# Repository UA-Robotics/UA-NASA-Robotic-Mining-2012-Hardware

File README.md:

# UA-NASA-Robotic-Mining-2012-Hardware

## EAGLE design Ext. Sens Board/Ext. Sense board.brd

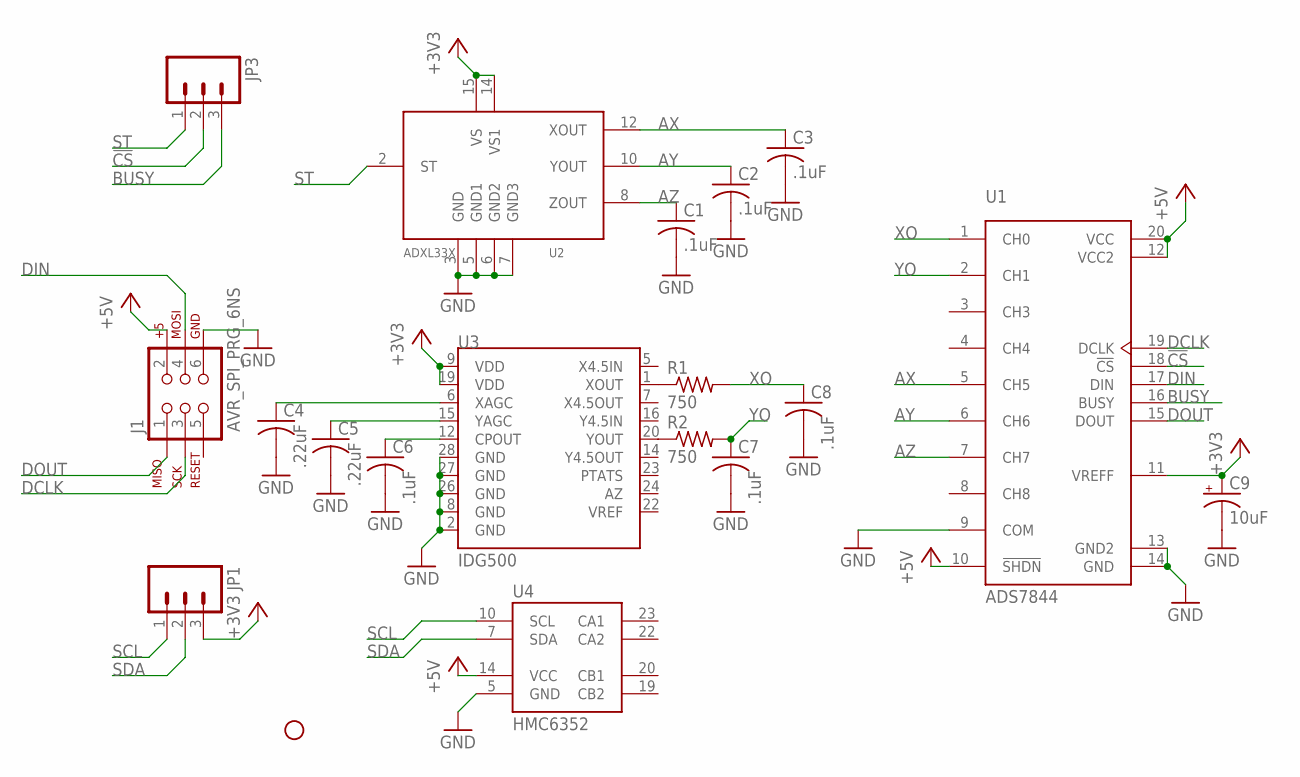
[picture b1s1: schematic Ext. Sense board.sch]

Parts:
C1, C2, C3, C6, C7, C8: .1uF; C0805
C4, C5: .22uF; C0805
C9: 10uF; POLC1206
J1: AVR_SPI_PRG_6NS; 2X3-NS
JP1, JP3: M031X03_NO_SILK; 1X03_NO_SILK
JP2: STAND-OFF
R1, R2: 750; R0805
U1: ADS7844; SSOP-20
U2: ADXL33X; 16LCSP
U3: IDG500; SPARKFUN_IDG500
U4: HMC6352; LCC24

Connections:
!CS: JP3.2, U1.18 (!CS)
+3V3: C9.1 (+), JP1.3, U1.11 (VREFF), U2.14 (VS1), U2.15 (VS), U3.9 (VDD), U3.19 (VDD)
+5V: J1.2, U1.10 (!SHDN), U1.12 (VCC2), U1.20 (VCC), U4.14 (VCC)
AX: C3.1, U1.5 (CH5), U2.12 (XOUT)
AY: C2.1, U1.6 (CH6), U2.10 (YOUT)
AZ: C1.1, U1.7 (CH7), U2.8 (ZOUT)
BUSY: JP3.3, U1.16 (BUSY)
DCLK: J1.3, U1.19 (DCLK)
DIN: J1.4, U1.17 (DIN)
DOUT: J1.1, U1.15 (DOUT)
GND: C1.2, C2.2, C3.2, C4.2, C5.2, C6.2, C7.2, C8.2, C9.2 (-), J1.6, U1.9 (COM), U1.13 (GND2), U1.14 (GND), U2.3 (GND), U2.5 (GND1), U2.6 (GND2), U2.7 (GND3), U3.2 (GND), U3.8 (GND), U3.26 (GND), U3.27 (GND), U3.28 (GND), U4.5 (GND)
unnamed: C4.1, U3.6 (XAGC)
unnamed: C5.1, U3.15 (YAGC)
unnamed: C6.1, U3.12 (CPOUT)
unnamed: R1.1, U3.1 (XOUT)
unnamed: R2.1, U3.20 (YOUT)
SCL: JP1.1, U4.10 (SCL)
SDA: JP1.2, U4.7 (SDA)
ST: JP3.1, U2.2 (ST)
XO: C8.1, R1.2, U1.1 (CH0)
YO: C7.1, R2.2, U1.2 (CH1)

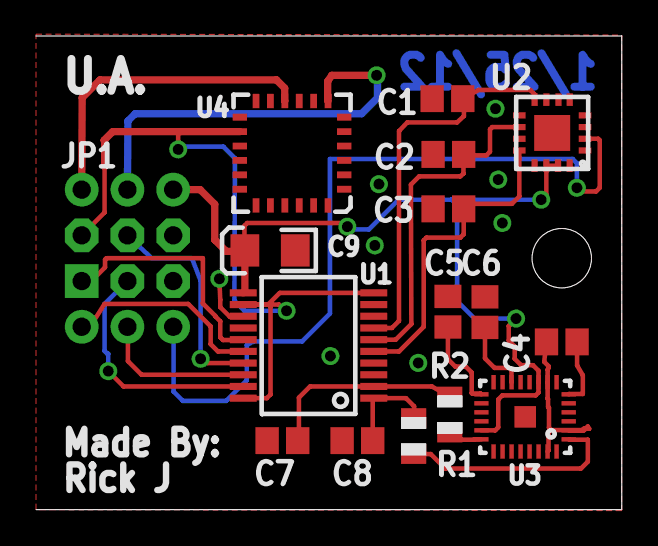
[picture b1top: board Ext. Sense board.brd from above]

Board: 2 copper layers, 32.5 x 26.3 mm, 19 parts (0 on the bottom side), 21 nets.

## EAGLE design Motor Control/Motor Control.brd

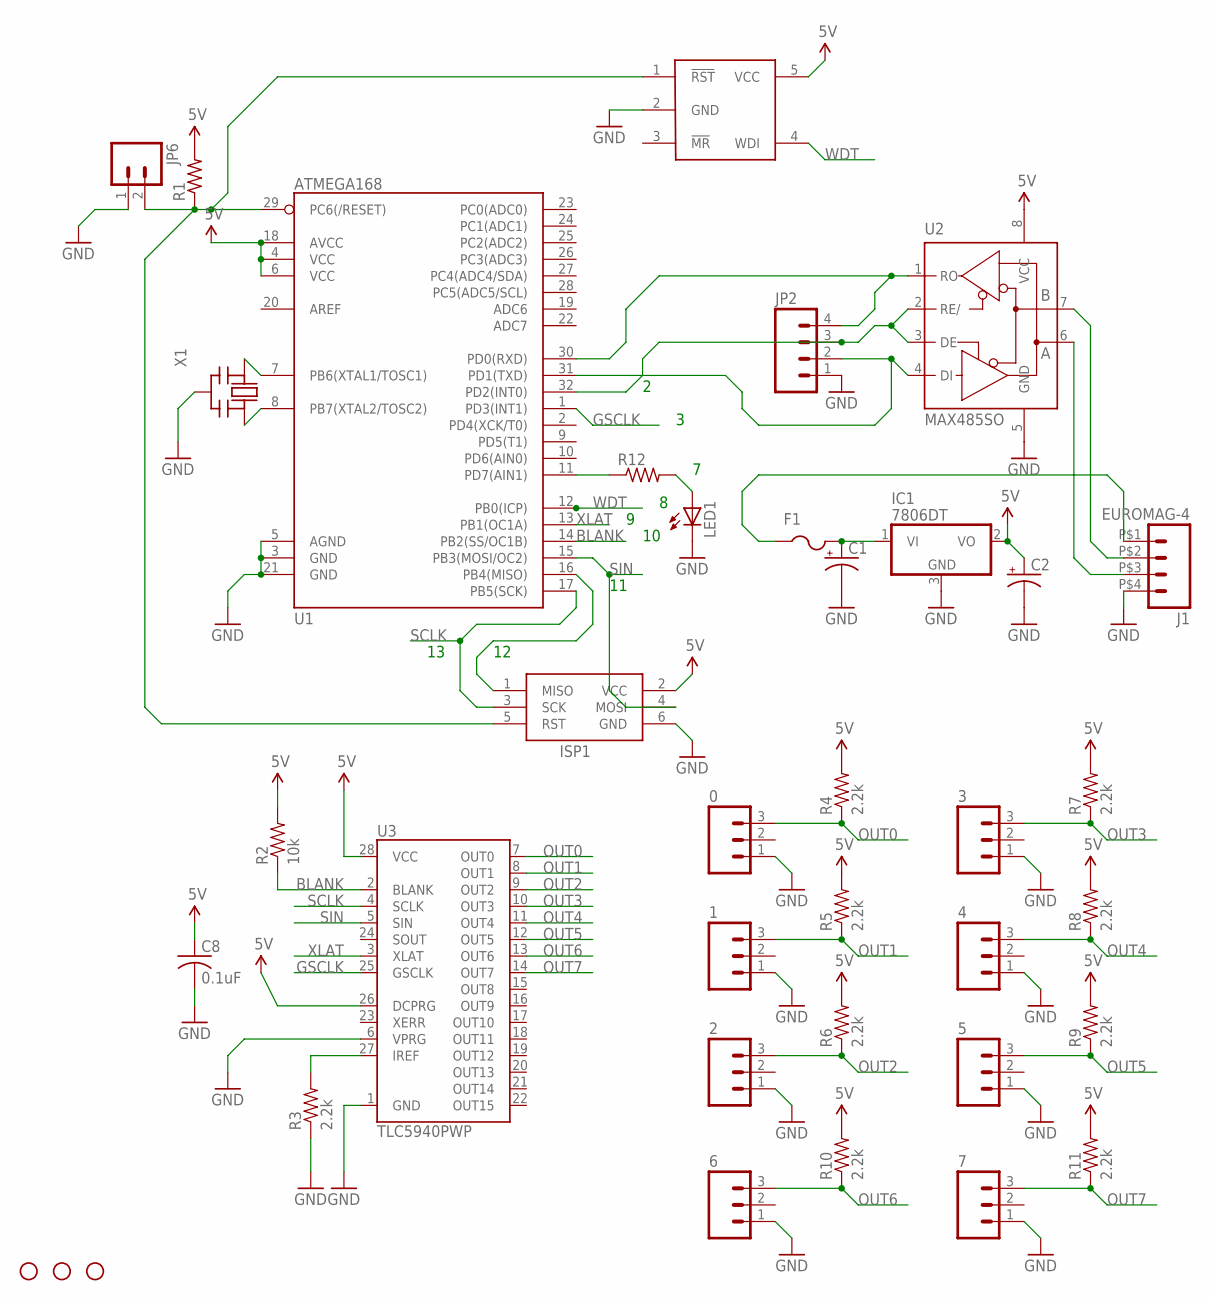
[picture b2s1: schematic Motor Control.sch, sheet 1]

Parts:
0, 1, 2, 3, 4, 5, 6, 7: M03PTH; 1X03
C1: CPOL-USCT7343; CT7343
C2: CPOL-USCT6032; CT6032
C8: 0.1uF; C0603
F1: PTCFUSE-1812; 1812
IC1: 7806DT; TO252
ISP1: AVRISP-6; AVRISP
J1: EUROMAG-4; M4
JP2: M04PTH; 1X04
JP3, JP4, JP5: STAND-OFF
JP6: M02LOCK_LONGPADS; 1X02_LOCK_LONGPADS
LED1: LEDCHIPLED_0805; CHIPLED_0805
R1, R12: R-US_M0805; M0805
R2: 10k; 0805
R3, R4, R5, R6, R7, R8, R9, R10, R11: 2.2k; 0805
U1: ATMEGA168; TQFP32-08
U2: MAX485SO; SO08
U3: TLC5940PWP; TSSOP28-GROUNDPAD
U$18: MAX823; SOT23-5L
X1: CERMOSCILL-AWCSR; AWCSR

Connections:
5V: C2.+, C8.1, IC1.2 (VO), ISP1.2 (VCC), R1.2, R2.2, R4.2, R5.2, R6.2, R7.2, R8.2, R9.2, R10.2, R11.2, U1.4 (VCC), U1.6 (VCC), U1.18 (AVCC), U2.8 (VCC), U3.26 (DCPRG), U3.28 (VCC), U$18.5 (VCC)
BLANK: R2.1, U1.14 (PB2(SS/OC1B)), U3.2 (BLANK)
GND: 0.1, 1.1, 2.1, 3.1, 4.1, 5.1, 6.1, 7.1, C1.-, C2.-, C8.2, IC1.3 (GND), ISP1.6 (GND), J1.P$4 (4), JP2.1, JP6.1, LED1.C, R3.1, U1.3 (GND), U1.5 (AGND), U1.21 (GND), U2.5 (GND), U3.1 (GND), U3.6 (VPRG), U$18.2 (GND), X1.2 (GND); also elsewhere on the board
GSCLK: U1.1 (PD3(INT1)), U3.25 (GSCLK)
unnamed: JP2.3, U1.32 (PD2(INT0)), U2.2 (RE/), U2.3 (DE)
unnamed: JP2.4, U1.30 (PD0(RXD)), U2.1 (RO)
unnamed: JP2.2, U1.31 (PD1(TXD)), U2.4 (DI)
unnamed: ISP1.5 (RST), JP6.2, R1.1, U1.29 (PC6(/RESET)), U$18.1 (!RST)
unnamed: U1.8 (PB7(XTAL2/TOSC2)), X1.3 (OUT)
unnamed: F1.1, J1.P$1 (1)
unnamed: ISP1.1 (MISO), U1.16 (PB4(MISO))
unnamed: C1.+, F1.2, IC1.1 (VI)
unnamed: U1.7 (PB6(XTAL1/TOSC1)), X1.1 (IN)
unnamed: R3.2, U3.27 (IREF)
unnamed: J1.P$2 (2), U2.7 (B)
unnamed: J1.P$3 (3), U2.6 (A)
unnamed: R12.1, U1.11 (PD7(AIN1))
unnamed: LED1.A, R12.2
OUT0: 0.3, R4.1, U3.7 (OUT0)
OUT1: 1.3, R5.1, U3.8 (OUT1)
OUT2: 2.3, R6.1, U3.9 (OUT2)
OUT3: 3.3, R7.1, U3.10 (OUT3)
OUT4: 4.3, R8.1, U3.11 (OUT4)
OUT5: 5.3, R9.1, U3.12 (OUT5)
OUT6: 6.3, R10.1, U3.13 (OUT6)
OUT7: 7.3, R11.1, U3.14 (OUT7)
SCLK: ISP1.3 (SCK), U1.17 (PB5(SCK)), U3.4 (SCLK)
SIN: ISP1.4 (MOSI), U1.15 (PB3(MOSI/OC2)), U3.5 (SIN)
WDT: U1.12 (PB0(ICP)), U$18.4 (WDI)
XLAT: U1.13 (PB1(OC1A)), U3.3 (XLAT)

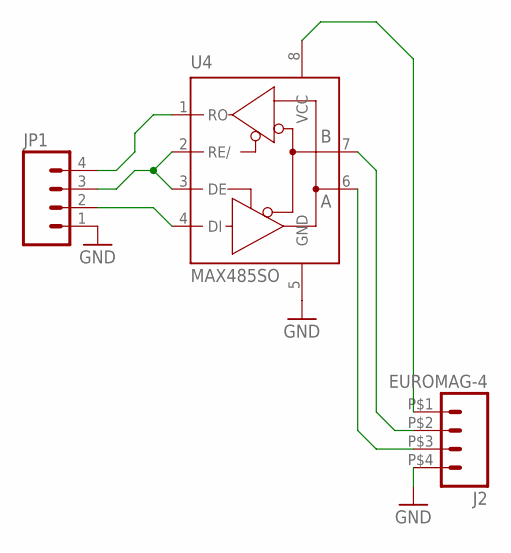
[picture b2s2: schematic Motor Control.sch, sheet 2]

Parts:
J2: EUROMAG-4; M4
JP1: M04PTH; 1X04
U4: MAX485SO; SO08

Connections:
GND: J2.P$4 (4), JP1.1, U4.5 (GND); also elsewhere on the board
unnamed: JP1.3, U4.2 (RE/), U4.3 (DE)
unnamed: JP1.4, U4.1 (RO)
unnamed: JP1.2, U4.4 (DI)
unnamed: J2.P$1 (1), U4.8 (VCC)
unnamed: J2.P$2 (2), U4.7 (B)
unnamed: J2.P$3 (3), U4.6 (A)

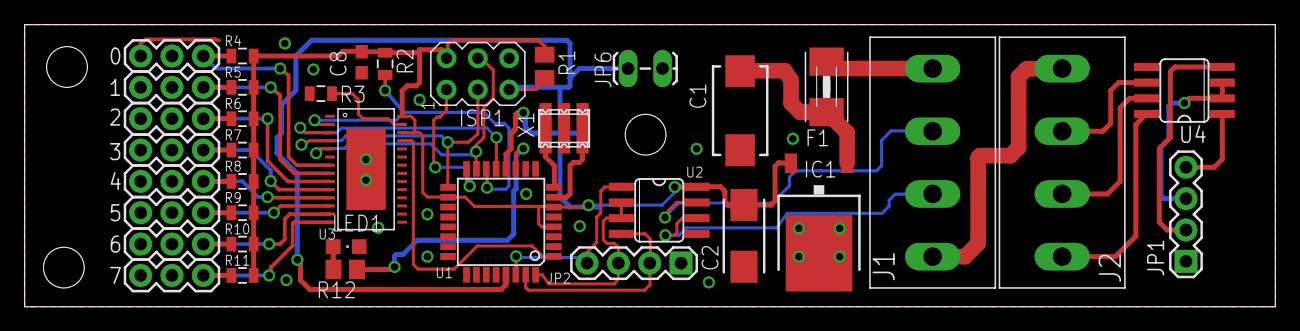
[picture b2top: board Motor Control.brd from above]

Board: 2 copper layers, 101.3 x 22.9 mm, 41 parts (1 on the bottom side), 36 nets.

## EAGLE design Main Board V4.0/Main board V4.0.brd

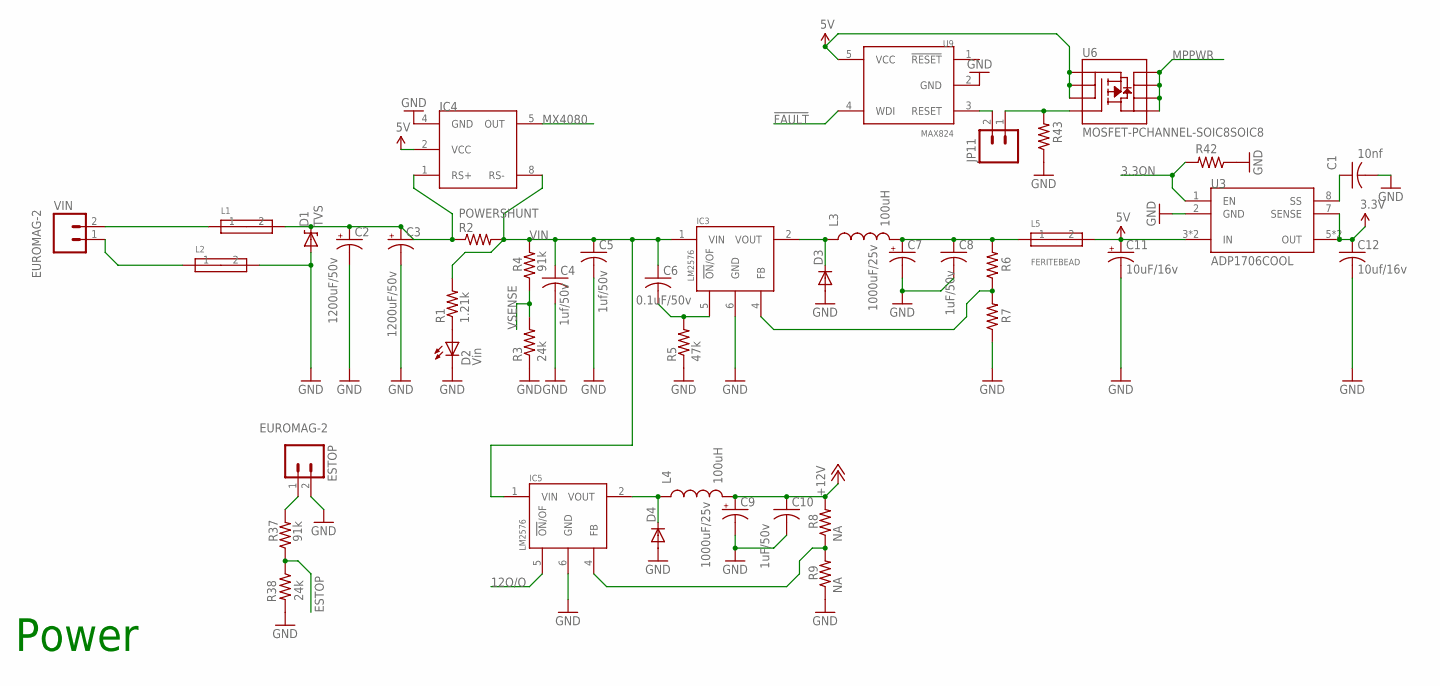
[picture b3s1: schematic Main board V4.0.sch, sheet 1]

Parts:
C1: 10nf; C0805
C2, C3: 1200uF/50v; CAN_18MM
C4, C5: 1uf/50v; C0805
C6: 0.1uF/50v; C0805
C7, C9: 1000uF/25v; CAN_18MM
C8, C10: 1uF/50v; C0805
C11: 10uF/16v; E3,5-10
C12: 10uf/16v; C0805
D1: TVS; DO-214AC
D2: Vin; CHIP-LED0805
D3, D4: DIODE-SMC; SMC
ESTOP: EUROMAG-2; M2
IC3, IC5: LM2576; TO-263-5
IC4: MAX4080; SO08
JP11: M02LOCK_LONGPADS; 1X02_LOCK_LONGPADS
L1, L2, L5: FERITEBEAD; 0603
L3, L4: 100uH; INDUCTOR_5X3
R1: 1.21k; R0805
R2: POWERSHUNT; RW3R5EAR100JE
R3, R38: 24k; R0805
R4, R37: 91k; R0805
R5: 47k; R0805
R6, R7, R8, R9, R42, R43: NA; R0805
U3: ADP1706COOL; SO-8COOL
U6: MOSFET-PCHANNEL-SOIC8SOIC8; SO08
U9: MAX824; SOT-5L
VIN: EUROMAG-2; M2

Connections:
3.3ON: R42.2, U3.1 (EN); also elsewhere on the board
3.3V: C12.1, U3.5 (OUT), U3.6 (OUT), U3.7 (SENSE); also elsewhere on the board
5V: C11.+, IC4.2 (VCC), L5.2, U3.3 (IN), U3.4 (IN), U6.1 (S), U6.2 (S), U6.3 (S), U9.5 (VCC); also elsewhere on the board
12O/O: IC5.5 (!ON!/OF); also elsewhere on the board
!FAULT: U9.4 (WDI); also elsewhere on the board
+12V: C9.+, C10.1, L4.2, R8.2; also elsewhere on the board
ESTOP: R37.1, R38.1; also elsewhere on the board
GND: C1.2, C2.-, C3.-, C4.2, C5.2, C7.-, C8.2, C9.-, C10.2, C11.-, C12.2, D1.A, D2.C, D3.A, D4.A, ESTOP.2, IC3.6 (GND), IC4.4 (GND), IC5.6 (GND), L2.2, R3.1, R5.1, R7.1, R9.1, R38.2, R42.1, R43.1, U3.2 (GND), U9.2 (GND); also elsewhere on the board
MPPWR: U6.5 (D), U6.6 (D), U6.7 (D), U6.8 (D); also elsewhere on the board
MX4080: IC4.5 (OUT); also elsewhere on the board
unnamed: C6.2, IC3.5 (!ON!/OF), R5.2
unnamed: D4.C, IC5.2 (VOUT), L4.1
unnamed: D3.C, IC3.2 (VOUT), L3.1
unnamed: JP11.1, R43.2, U6.4 (G)
unnamed: JP11.2, U9.3 (RESET)
unnamed: L1.1, VIN.2
unnamed: ESTOP.1, R37.2
unnamed: C2.+, C3.+, D1.C, IC4.1 (RS+), L1.2, R2.1
unnamed: IC3.4 (FB), R6.1, R7.2
unnamed: IC5.4 (FB), R8.1, R9.2
unnamed: D2.A, R1.1
unnamed: L2.1, VIN.1
unnamed: C7.+, C8.1, L3.2, L5.1, R6.2
unnamed: C1.1, U3.8 (SS)
VIN: C4.1, C5.1, C6.1, IC3.1 (VIN), IC4.8 (RS-), IC5.1 (VIN), R1.2, R2.2, R4.2
VSENSE: R3.2, R4.1; also elsewhere on the board

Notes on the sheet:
Power
IC4

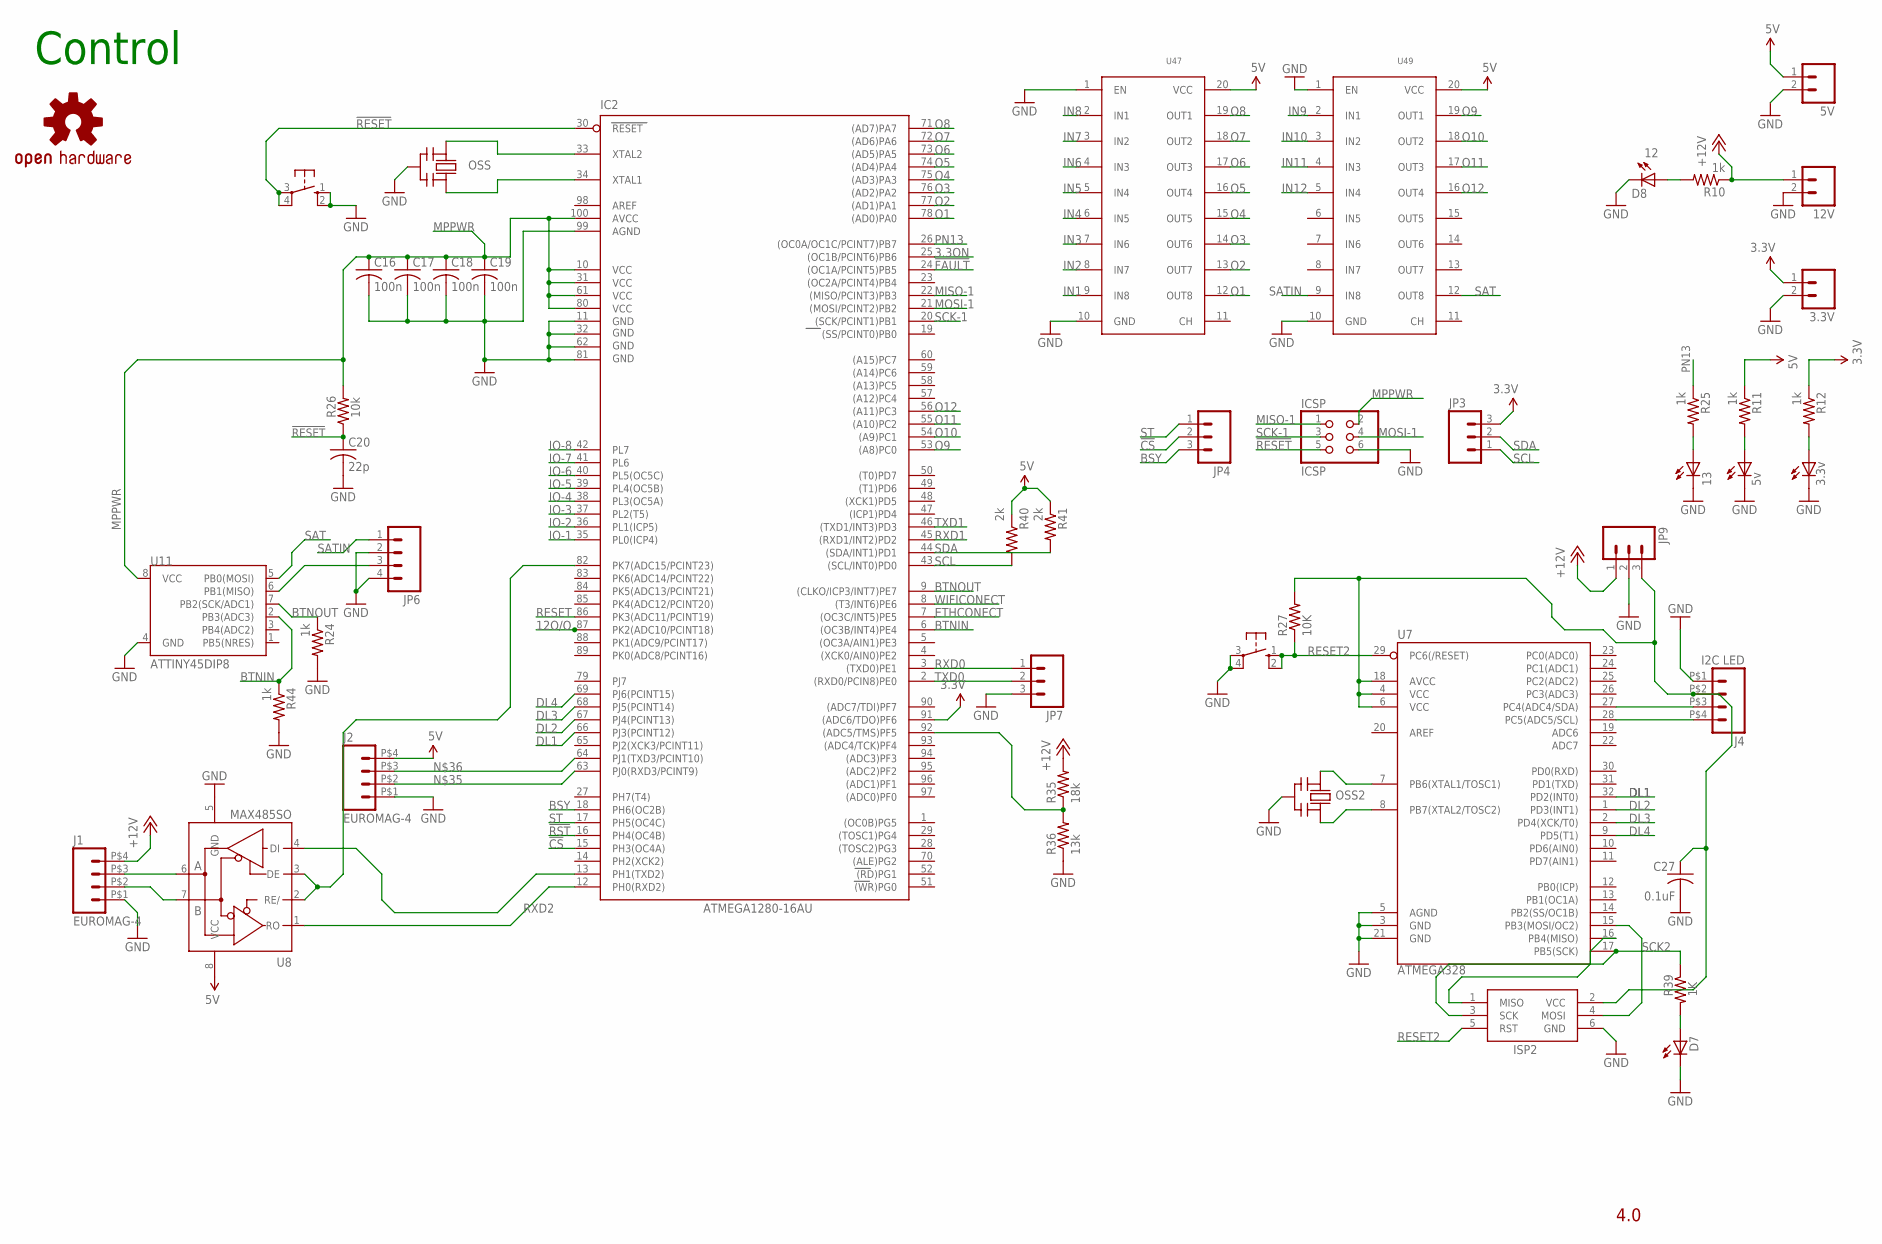
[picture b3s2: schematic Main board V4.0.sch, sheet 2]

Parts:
3.3V, 5V, 12V: EUROMAG-2; M2
13: LEDCHIP-LED0805; CHIP-LED0805
C16, C17, C18, C19: 100n; C0805
C20: 22p; C0805
C27: 0.1uF; C0805
D5: 5v; CHIP-LED0805
D6: 3.3v; CHIP-LED0805
D7: LEDCHIP-LED0805; CHIP-LED0805
D8: 12; CHIP-LED0805
IC2: ATMEGA1280-16AU; TQFP100
ICSP: ICSP; 2X03
ISP2: AVRISP-6; AVRISP
J1, J2: EUROMAG-4; M4
J4: I2C LED; M4
JP3, JP4: M03PTH; 1X03
JP6: M04LOCK_LONGPADS; 1X04_LOCK_LONGPADS
JP7: M03LOCK; 1X03_LOCK
JP9: M03LOCK_LONGPADS; 1X03_LOCK_LONGPADS
OSS, OSS2: CERMOSCILL-AWCSR; AWCSR
R10, R11, R12, R24, R25, R44: 1k; R0805
R26: 10k; R0805
R27: 10K; 0805
R35: 18k; R0805
R36: 13k; R0805
R39: 1K; 0805
R40, R41: 2k; R0805
S1, S4: 10-XX; B3F-10XX
U7: ATMEGA328; TQFP32-08
U8: MAX485SO; SO08
U11: ATTINY45DIP8; DIP08
U47, U49: MAX6818; SSOP-20
U$3: OSHW-LOGOL; OSHW-LOGO-L

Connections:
3.3ON: IC2.25 ((OC1B/PCINT6)PB6); also elsewhere on the board
3.3V: 3.3V.1, IC2.91 ((ADC6/TDO)PF6), JP3.3, R12.1; also elsewhere on the board
5V: 5V.1, J2.P$4 (4), R11.1, R40.1, R41.1, U8.8 (VCC), U47.20 (VCC), U49.20 (VCC); also elsewhere on the board
12O/O: IC2.87 (PK2(ADC10/PCINT18)); also elsewhere on the board
!CS: IC2.15 (PH3(OC4A)), JP4.2
!FAULT: IC2.24 ((OC1A/PCINT5)PB5); also elsewhere on the board
!RESET: C20.1, IC2.30 (RESET), ICSP.5, R26.1, S1.3, S1.4 (P1)
!RST: IC2.16 (PH4(OC4B)); also elsewhere on the board
+12V: 12V.1, J1.P$4 (4), JP9.1, R10.1, R35.2; also elsewhere on the board
BSY: IC2.18 (PH6(OC2B)), JP4.3
BTNIN: IC2.6 ((OC3B/INT4)PE4), R44.1, U11.2 (PB3(ADC3))
BTNOUT: IC2.9 ((CLKO/ICP3/INT7)PE7), R24.1, U11.7 (PB2(SCK/ADC1))
DL1: IC2.66 (PJ3(PCINT12)), U7.32 (PD2(INT0))
DL2: IC2.67 (PJ4(PCINT13)), U7.1 (PD3(INT1))
DL3: IC2.68 (PJ5(PCINT14)), U7.2 (PD4(XCK/T0))
DL4: IC2.69 (PJ6(PCINT15)), U7.9 (PD5(T1))
ETHCONECT: IC2.7 ((OC3C/INT5)PE5); also elsewhere on the board
GND: 3.3V.2, 5V.2, 12V.2, 13.C, C16.2, C17.2, C18.2, C19.2, C20.2, C27.2, D5.C, D6.C, D7.C, D8.C, IC2.11 (GND), IC2.32 (GND1), IC2.62 (GND2), IC2.81 (GND3), IC2.99 (AGND), ICSP.6, ISP2.6 (GND), J1.P$1 (1), J2.P$1 (1), J4.P$1 (1), JP6.2, JP6.4, JP7.3, JP9.2, OSS.2 (GND), OSS2.2 (GND), R24.2, R36.1, R44.2, S1.1 (S), S1.2 (S1), S4.3, S4.4 (P1), U7.3 (GND), U7.5 (AGND), U7.21 (GND), U8.5 (GND), U11.4 (GND), U47.1 (EN), U47.10 (GND), U49.1 (EN), U49.10 (GND); also elsewhere on the board
IN1: U47.9 (IN8); also elsewhere on the board
IN2: U47.8 (IN7); also elsewhere on the board
IN3: U47.7 (IN6); also elsewhere on the board
IN4: U47.6 (IN5); also elsewhere on the board
IN5: U47.5 (IN4); also elsewhere on the board
IN6: U47.4 (IN3); also elsewhere on the board
IN7: U47.3 (IN2); also elsewhere on the board
IN8: U47.2 (IN1); also elsewhere on the board
IN9: U49.2 (IN1); also elsewhere on the board
IN10: U49.3 (IN2); also elsewhere on the board
IN11: U49.4 (IN3); also elsewhere on the board
IN12: U49.5 (IN4); also elsewhere on the board
IO-1: IC2.35 (PL0(ICP4)); also elsewhere on the board
IO-2: IC2.36 (PL1(ICP5)); also elsewhere on the board
IO-3: IC2.37 (PL2(T5)); also elsewhere on the board
IO-4: IC2.38 (PL3(OC5A)); also elsewhere on the board
IO-5: IC2.39 (PL4(OC5B)); also elsewhere on the board
IO-6: IC2.40 (PL5(OC5C)); also elsewhere on the board
IO-7: IC2.41 (PL6); also elsewhere on the board
IO-8: IC2.42 (PL7); also elsewhere on the board
MISO-1: IC2.22 ((MISO/PCINT3)PB3), ICSP.1
MOSI-1: IC2.21 ((MOSI/PCINT2)PB2), ICSP.4
MPPWR: C16.1, C17.1, C18.1, C19.1, IC2.10 (VCC), IC2.31 (VCC1), IC2.61 (VCC2), IC2.80 (VCC3), IC2.100 (AVCC), ICSP.2, R26.2, U11.8 (VCC); also elsewhere on the board
unnamed: 13.A, R25.2
unnamed: D5.A, R11.2
unnamed: IC2.34 (XTAL1), OSS.3 (OUT)
unnamed: IC2.33 (XTAL2), OSS.1 (IN)
unnamed: IC2.92 ((ADC5/TMS)PF5), R35.1, R36.2
unnamed: D8.A, R10.2
unnamed: D6.A, R12.2
unnamed: IC2.63 (PJ0(RXD3/PCINT9)), J2.P$2 (2)
unnamed: IC2.64 (PJ1(TXD3/PCINT10)), J2.P$3 (3)
unnamed: D7.A, R39.2
unnamed: OSS2.3 (OUT), U7.8 (PB7(XTAL2/TOSC2))
unnamed: JP6.3, U11.6 (PB1(MISO))
unnamed: OSS2.1 (IN), U7.7 (PB6(XTAL1/TOSC1))
unnamed: J4.P$4 (4), U7.28 (PC5(ADC5/SCL))
unnamed: ISP2.4 (MOSI), U7.15 (PB3(MOSI/OC2))
unnamed: ISP2.1 (MISO), U7.16 (PB4(MISO))
unnamed: J4.P$3 (3), U7.27 (PC4(ADC4/SDA))
unnamed: C27.1, ISP2.2 (VCC), J4.P$2 (2), JP9.3, R27.2, U7.4 (VCC), U7.6 (VCC), U7.18 (AVCC)
unnamed: J1.P$3 (3), U8.6 (A)
unnamed: J1.P$2 (2), U8.7 (B)
unnamed: IC2.82 (PK7(ADC15/PCINT23)), U8.2 (RE/), U8.3 (DE)
O1: IC2.78 ((AD0)PA0), U47.12 (OUT8)
O2: IC2.77 ((AD1)PA1), U47.13 (OUT7)
O3: IC2.76 ((AD2)PA2), U47.14 (OUT6)
O4: IC2.75 ((AD3)PA3), U47.15 (OUT5)
O5: IC2.74 ((AD4)PA4), U47.16 (OUT4)
O6: IC2.73 ((AD5)PA5), U47.17 (OUT3)
O7: IC2.72 ((AD6)PA6), U47.18 (OUT2)
O8: IC2.71 ((AD7)PA7), U47.19 (OUT1)
O9: IC2.53 ((A8)PC0), U49.19 (OUT1)
O10: IC2.54 ((A9)PC1), U49.18 (OUT2)
O11: IC2.55 ((A10)PC2), U49.17 (OUT3)
O12: IC2.56 ((A11)PC3), U49.16 (OUT4)
PN13: IC2.26 ((OC0A/OC1C/PCINT7)PB7), R25.1
RESET: IC2.86 (PK3(ADC11/PCINT19)); also elsewhere on the board
RESET2: ISP2.5 (RST), R27.1, S4.1 (S), S4.2 (S1), U7.29 (PC6(/RESET))
RXD0: IC2.3 ((TXD0)PE1), JP7.1; also elsewhere on the board
RXD1: IC2.45 ((RXD1/INT2)PD2); also elsewhere on the board
RXD2: IC2.12 (PH0(RXD2)), U8.1 (RO)
SAT: U11.5 (PB0(MOSI)), U49.12 (OUT8)
SATIN: JP6.1, U49.9 (IN8)
SCK2: ISP2.3 (SCK), R39.1, U7.17 (PB5(SCK))
SCK-1: IC2.20 ((SCK/PCINT1)PB1), ICSP.3
SCL: IC2.43 ((SCL/INT0)PD0), JP3.1, R40.2; also elsewhere on the board
SDA: IC2.44 ((SDA/INT1)PD1), JP3.2, R41.2; also elsewhere on the board
ST: IC2.17 (PH5(OC4C)), JP4.1
TXD0: IC2.2 ((RXD0/PCIN8)PE0), JP7.2; also elsewhere on the board
TXD1: IC2.46 ((TXD1/INT3)PD3); also elsewhere on the board
TXD2: IC2.13 (PH1(TXD2)), U8.4 (DI)
WIFICONECT: IC2.8 ((T3/INT6)PE6); also elsewhere on the board

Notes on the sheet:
4.0
Control

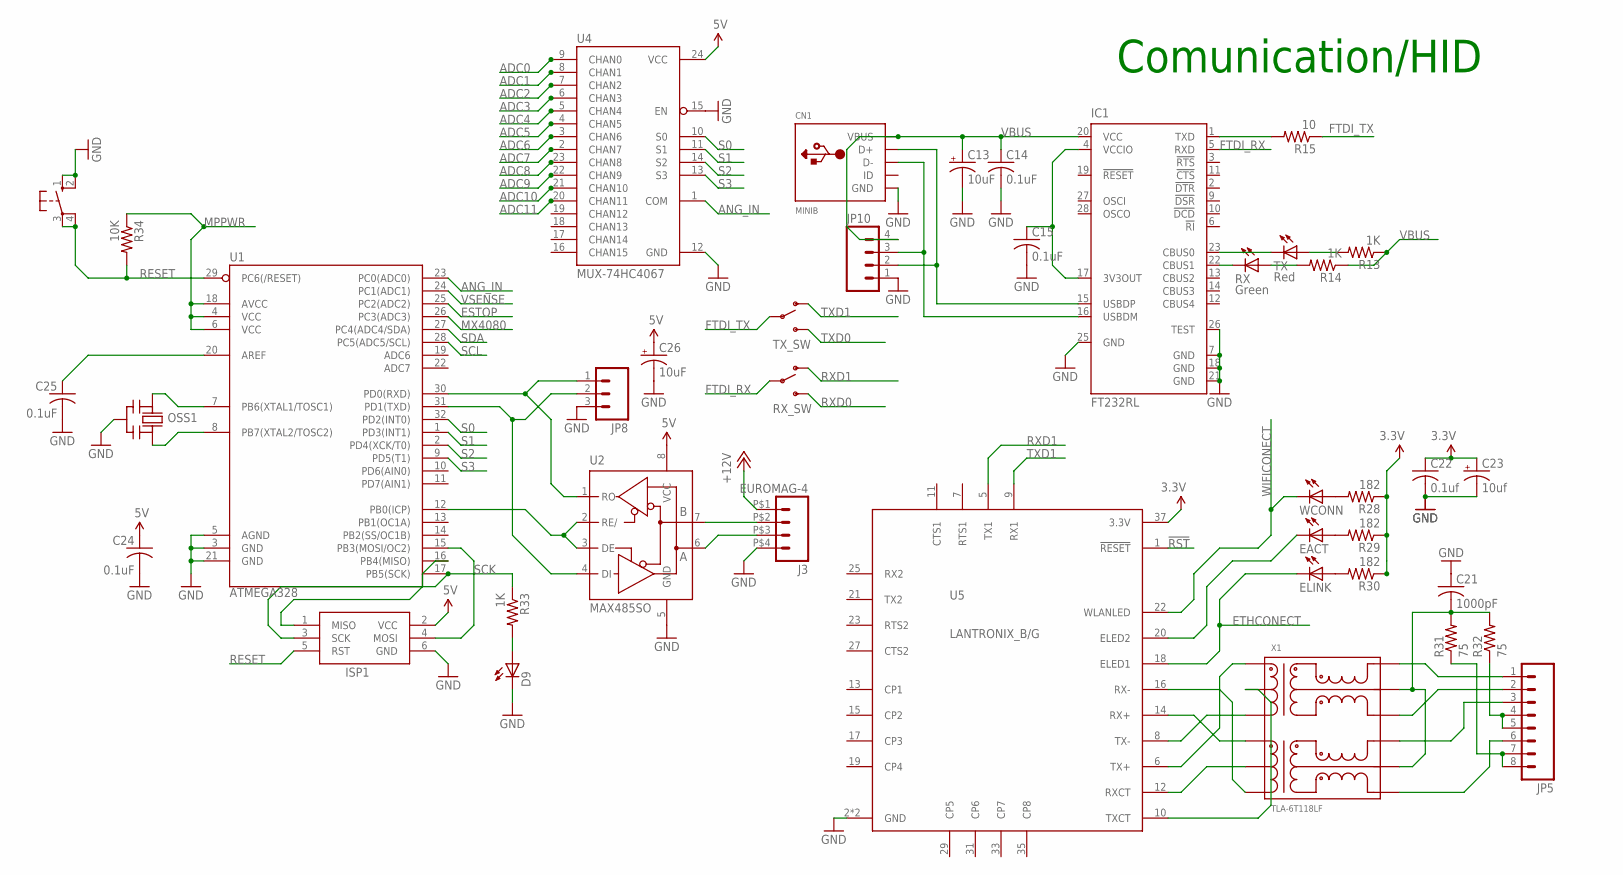
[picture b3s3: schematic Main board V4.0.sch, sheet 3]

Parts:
C13: 10uF; A/3216-18R
C14, C15, C24: 0.1uF; C0805K
C21: 1000pF; C1812
C22: 0.1uf; C0805K
C23: 10uf; EIA3528
C25: 0.1uF; C0805
C26: 10uF; EIA3528
CN1: MINIB; USB-MINIB
D9: LEDCHIP-LED0805; CHIP-LED0805
EACT: LEDCHIP-LED0805; CHIP-LED0805
ELINK: LEDCHIP-LED0805; CHIP-LED0805
IC1: FT232RL; SSOP28
ISP1: AVRISP-6; AVRISP
J3: EUROMAG-4; M4
JP5: M08LOCK_LONGPADS; 1X08_LOCK_LONGPADS
JP8: M03LOCK; 1X03_LOCK
JP10: M04LONGPADS; 1X04_LONGPADS
OSS1: CERMOSCILL-AWCSR; AWCSR
R13, R14, R33: 1K; R0805
R15: 10; R0805
R28, R29, R30: 182; R0805
R31, R32: 75; R0805
R34: 10K; R0805
RX: Green; CHIP-LED0805
RX_SW: SWITCH-SPSTKIT; SWITCH-SPDT_KIT
S3: 10-XX; B3F-10XX
TX: Red; CHIP-LED0805
TX_SW: SWITCH-SPSTKIT; SWITCH-SPDT_KIT
U1: ATMEGA328; TQFP32-08
U2: MAX485SO; SO08
U4: MUX-74HC4067; SSOP24
U5: LANTRONIX_B/G; LANA/BTH
WCONN: LEDCHIP-LED0805; CHIP-LED0805
X1: TLA-6T118LF; SO-16MOD

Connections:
3.3V: C22.1, C23.A (+), R28.1, R29.1, R30.1, U5.37 (3.3V); also elsewhere on the board
5V: C24.1, C26.A (+), ISP1.2 (VCC), U2.8 (VCC), U4.24 (VCC); also elsewhere on the board
!RST: U5.1 (!RESET); also elsewhere on the board
+12V: J3.P$1 (1); also elsewhere on the board
ADC0: U4.9 (CHAN0); also elsewhere on the board
ADC1: U4.8 (CHAN1); also elsewhere on the board
ADC2: U4.7 (CHAN2); also elsewhere on the board
ADC3: U4.6 (CHAN3); also elsewhere on the board
ADC4: U4.5 (CHAN4); also elsewhere on the board
ADC5: U4.4 (CHAN5); also elsewhere on the board
ADC6: U4.3 (CHAN6); also elsewhere on the board
ADC7: U4.2 (CHAN7); also elsewhere on the board
ADC8: U4.23 (CHAN8); also elsewhere on the board
ADC9: U4.22 (CHAN9); also elsewhere on the board
ADC10: U4.21 (CHAN10); also elsewhere on the board
ADC11: U4.20 (CHAN11); also elsewhere on the board
ANG_IN: U1.23 (PC0(ADC0)), U4.1 (COM)
ESTOP: U1.25 (PC2(ADC2)); also elsewhere on the board
ETHCONECT: ELINK.C, U5.18 (ELED1); also elsewhere on the board
FTDI_RX: IC1.5 (RXD), RX_SW.2
FTDI_TX: R15.1, TX_SW.2
GND: C13.-, C14.2, C15.2, C21.1, C22.2, C23.C (-), C24.2, C25.2, C26.C (-), CN1.GND, D9.C, IC1.7 (GND), IC1.18 (GND), IC1.21 (GND), IC1.25 (GND), IC1.26 (TEST), ISP1.6 (GND), J3.P$4 (4), JP8.3, JP10.1, OSS1.2 (GND), S3.1 (S), S3.2 (S1), U1.3 (GND), U1.5 (AGND), U1.21 (GND), U2.5 (GND), U4.12 (GND), U4.15 (EN), U5.2 (GND), U5.39 (GND); also elsewhere on the board
MPPWR: R34.1, U1.4 (VCC), U1.6 (VCC), U1.18 (AVCC); also elsewhere on the board
MX4080: U1.26 (PC3(ADC3)); also elsewhere on the board
unnamed: CN1.D+, IC1.15 (USBDP), JP10.2
unnamed: CN1.D-, IC1.16 (USBDM), JP10.3
unnamed: IC1.23 (CBUS0), TX.C
unnamed: D9.A, R33.2
unnamed: IC1.22 (CBUS1), RX.C
unnamed: R14.2, RX.A
unnamed: R13.2, TX.A
unnamed: IC1.1 (TXD), R15.2
unnamed: C15.1, IC1.4 (VCCIO), IC1.17 (3V3OUT)
unnamed: OSS1.3 (OUT), U1.8 (PB7(XTAL2/TOSC2))
unnamed: OSS1.1 (IN), U1.7 (PB6(XTAL1/TOSC1))
unnamed: C25.1, U1.20 (AREF)
unnamed: ISP1.4 (MOSI), U1.15 (PB3(MOSI/OC2))
unnamed: ISP1.1 (MISO), U1.16 (PB4(MISO))
unnamed: J3.P$2 (2), U2.7 (B)
unnamed: J3.P$3 (3), U2.6 (A)
unnamed: U1.12 (PB0(ICP)), U2.2 (RE/), U2.3 (DE)
unnamed: JP8.1, U1.30 (PD0(RXD)), U2.1 (RO)
unnamed: JP8.2, U1.31 (PD1(TXD)), U2.4 (DI)
unnamed: U5.8 (TX-), X1.3
unnamed: U5.6 (TX+), X1.1
unnamed: U5.14 (RX+), X1.6
unnamed: U5.16 (RX-), X1.8
unnamed: U5.12 (RXCT), X1.7
unnamed: U5.10 (TXCT), X1.2
unnamed: JP5.4, JP5.5, R32.1
unnamed: JP5.7, JP5.8, R31.1
unnamed: JP5.6, X1.9
unnamed: JP5.3, X1.11
unnamed: JP5.2, X1.14
unnamed: JP5.1, X1.16
unnamed: C21.2, R31.2, R32.2, X1.10, X1.15
unnamed: ELINK.A, R30.2
unnamed: EACT.A, R29.2
unnamed: R28.2, WCONN.A
unnamed: EACT.C, U5.20 (ELED2)
RESET: ISP1.5 (RST), R34.2, S3.3, S3.4 (P1), U1.29 (PC6(/RESET)); also elsewhere on the board
RXD0: RX_SW.3 (S); also elsewhere on the board
RXD1: RX_SW.1 (O), U5.5 (TX1); also elsewhere on the board
S0: U1.32 (PD2(INT0)), U4.10 (S0)
S1: U1.1 (PD3(INT1)), U4.11 (S1)
S2: U1.2 (PD4(XCK/T0)), U4.14 (S2)
S3: U1.9 (PD5(T1)), U4.13 (S3)
SCK: ISP1.3 (SCK), R33.1, U1.17 (PB5(SCK))
SCL: U1.28 (PC5(ADC5/SCL)); also elsewhere on the board
SDA: U1.27 (PC4(ADC4/SDA)); also elsewhere on the board
TXD0: TX_SW.3 (S); also elsewhere on the board
TXD1: TX_SW.1 (O), U5.9 (RX1); also elsewhere on the board
VBUS: C13.+, C14.1, CN1.VBUS, IC1.20 (VCC), JP10.4, R13.1, R14.1
VSENSE: U1.24 (PC1(ADC1)); also elsewhere on the board
WIFICONECT: U5.22 (WLANLED), WCONN.C; also elsewhere on the board

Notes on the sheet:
Comunication/HID

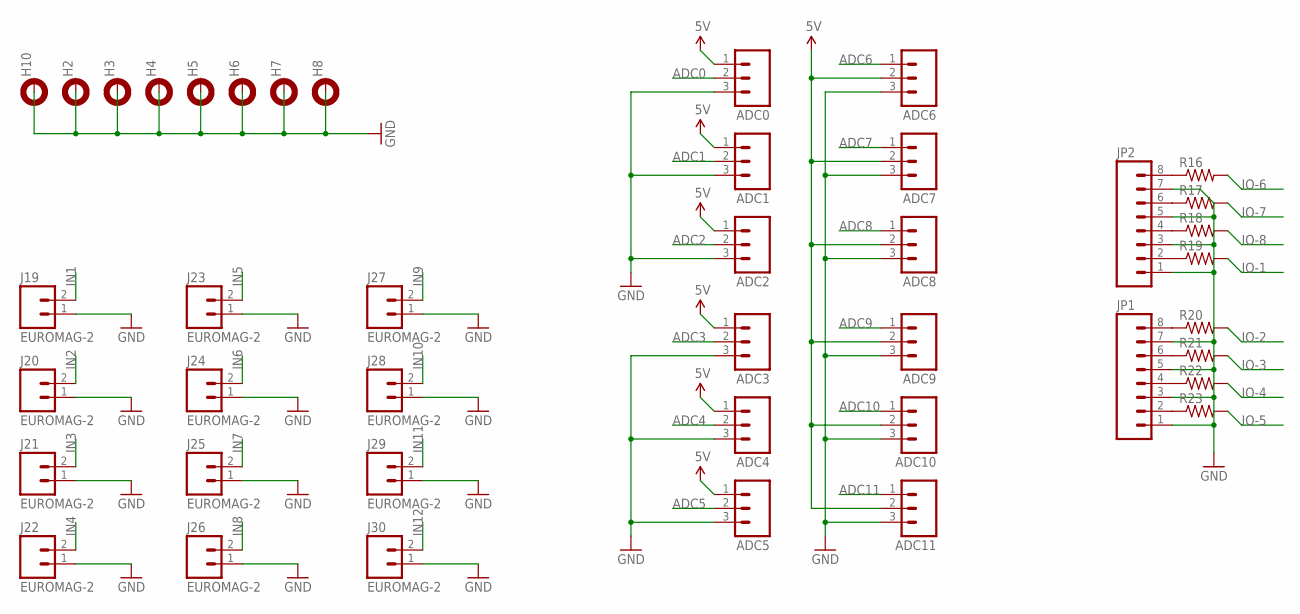
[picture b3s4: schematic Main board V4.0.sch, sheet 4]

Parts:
ADC0, ADC1, ADC2, ADC3, ADC4, ADC5: EUROMAG-390DEG; M3
ADC6, ADC7, ADC8, ADC9, ADC10, ADC11: M03PTH; 1X03
H2, H3, H4, H5, H6, H7, H8, H10: MOUNT-PAD-ROUND2.8; 2,8-PAD
J19, J20, J21, J22, J23, J24, J25, J26, J27, J28, J29, J30: EUROMAG-2; M2
JP1, JP2: M08LOCK; 1X08_LOCK
R16, R17, R18, R19, R20, R21, R22, R23: R-US_FLIPFLOP; 0805-THM

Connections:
5V: ADC0.1, ADC1.1, ADC2.1, ADC3.1, ADC4.1, ADC5.1, ADC6.2, ADC7.2, ADC8.2, ADC9.2, ADC10.2, ADC11.2; also elsewhere on the board
ADC0: ADC0.2; also elsewhere on the board
ADC1: ADC1.2; also elsewhere on the board
ADC2: ADC2.2; also elsewhere on the board
ADC3: ADC3.2; also elsewhere on the board
ADC4: ADC4.2; also elsewhere on the board
ADC5: ADC5.2; also elsewhere on the board
ADC6: ADC6.1; also elsewhere on the board
ADC7: ADC7.1; also elsewhere on the board
ADC8: ADC8.1; also elsewhere on the board
ADC9: ADC9.1; also elsewhere on the board
ADC10: ADC10.1; also elsewhere on the board
ADC11: ADC11.1; also elsewhere on the board
GND: ADC0.3, ADC1.3, ADC2.3, ADC3.3, ADC4.3, ADC5.3, ADC6.3, ADC7.3, ADC8.3, ADC9.3, ADC10.3, ADC11.3, H2.B2,8, H3.B2,8, H4.B2,8, H5.B2,8, H6.B2,8, H7.B2,8, H8.B2,8, H10.B2,8, J19.1, J20.1, J21.1, J22.1, J23.1, J24.1, J25.1, J26.1, J27.1, J28.1, J29.1, J30.1, JP1.1, JP1.3, JP1.5, JP1.7, JP2.1, JP2.3, JP2.5, JP2.7; also elsewhere on the board
IN1: J19.2; also elsewhere on the board
IN2: J20.2; also elsewhere on the board
IN3: J21.2; also elsewhere on the board
IN4: J22.2; also elsewhere on the board
IN5: J23.2; also elsewhere on the board
IN6: J24.2; also elsewhere on the board
IN7: J25.2; also elsewhere on the board
IN8: J26.2; also elsewhere on the board
IN9: J27.2; also elsewhere on the board
IN10: J28.2; also elsewhere on the board
IN11: J29.2; also elsewhere on the board
IN12: J30.2; also elsewhere on the board
IO-1: R19.2; also elsewhere on the board
IO-2: R20.2; also elsewhere on the board
IO-3: R21.2; also elsewhere on the board
IO-4: R22.2; also elsewhere on the board
IO-5: R23.2; also elsewhere on the board
IO-6: R16.2; also elsewhere on the board
IO-7: R17.2; also elsewhere on the board
IO-8: R18.2; also elsewhere on the board
unnamed: JP1.8, R20.1
unnamed: JP1.6, R21.1
unnamed: JP1.4, R22.1
unnamed: JP1.2, R23.1
unnamed: JP2.2, R19.1
unnamed: JP2.4, R18.1
unnamed: JP2.6, R17.1
unnamed: JP2.8, R16.1

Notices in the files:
parts and their libraries:
SparkFun: Licensing: CC v3.0 Share-Alike You are welcome to use this library for commercial purposes.
